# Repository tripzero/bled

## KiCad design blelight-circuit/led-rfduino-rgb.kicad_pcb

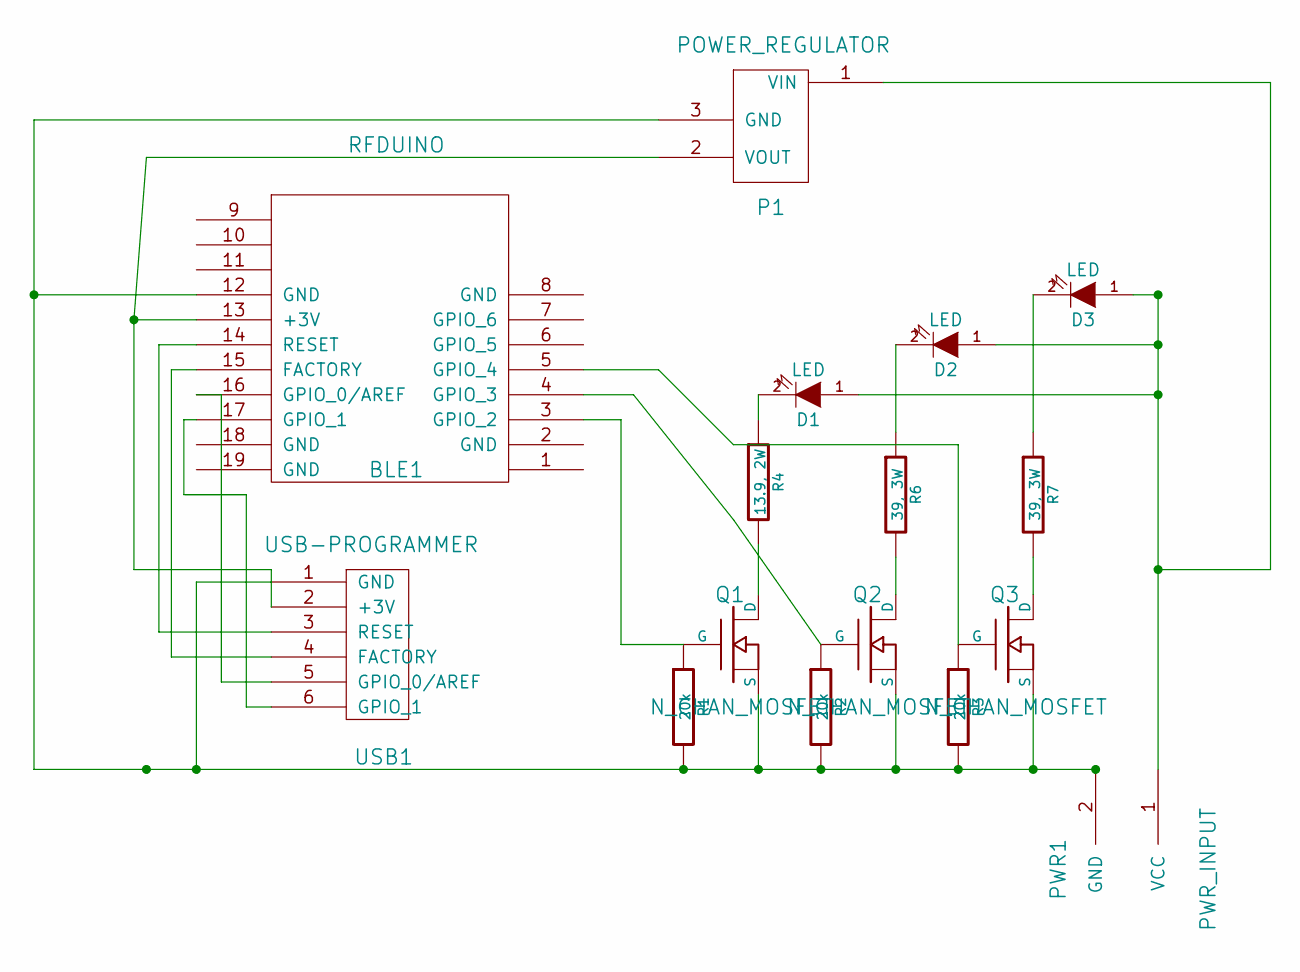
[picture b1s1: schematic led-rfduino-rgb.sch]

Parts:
BLE1: RFDUINO
D1, D2, D3: LED
P1: POWER_REGULATOR
PWR1: PWR_INPUT
Q1, Q2, Q3: N_CHAN_MOSFET
R1, R2, R3: 20k
R4: 13.9, 2W
R6, R7: 39, 3W
USB1: USB-PROGRAMMER

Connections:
unnamed: BLE1.14 (RESET), USB1.3 (RESET)
unnamed: Q3.3 (D), R7.2
unnamed: BLE1.5 (GPIO_4), Q3.2 (G), R3.1
unnamed: Q2.3 (D), R6.2
unnamed: Q1.3 (D), R4.2
unnamed: BLE1.3 (GPIO_2), Q1.2 (G), R1.1
unnamed: BLE1.4 (GPIO_3), Q2.2 (G), R2.1
unnamed: D1.2 (K), R4.1
unnamed: D2.2 (K), R6.1
unnamed: D3.2 (K), R7.1
unnamed: BLE1.17 (GPIO_1), USB1.6 (GPIO_1)
unnamed: BLE1.16 (GPIO_0/AREF), USB1.5 (GPIO_0/AREF)
unnamed: BLE1.15 (FACTORY), USB1.4 (FACTORY)
unnamed: BLE1.13 (+3V), P1.2 (VOUT), USB1.2 (+3V)
unnamed: BLE1.12 (GND), P1.3 (GND), PWR1.2 (GND), Q1.1 (S), Q2.1 (S), Q3.1 (S), R1.2, R2.2, R3.2, USB1.1 (GND)
unnamed: D1.1 (A), D2.1 (A), D3.1 (A), P1.1 (VIN), PWR1.1 (VCC)

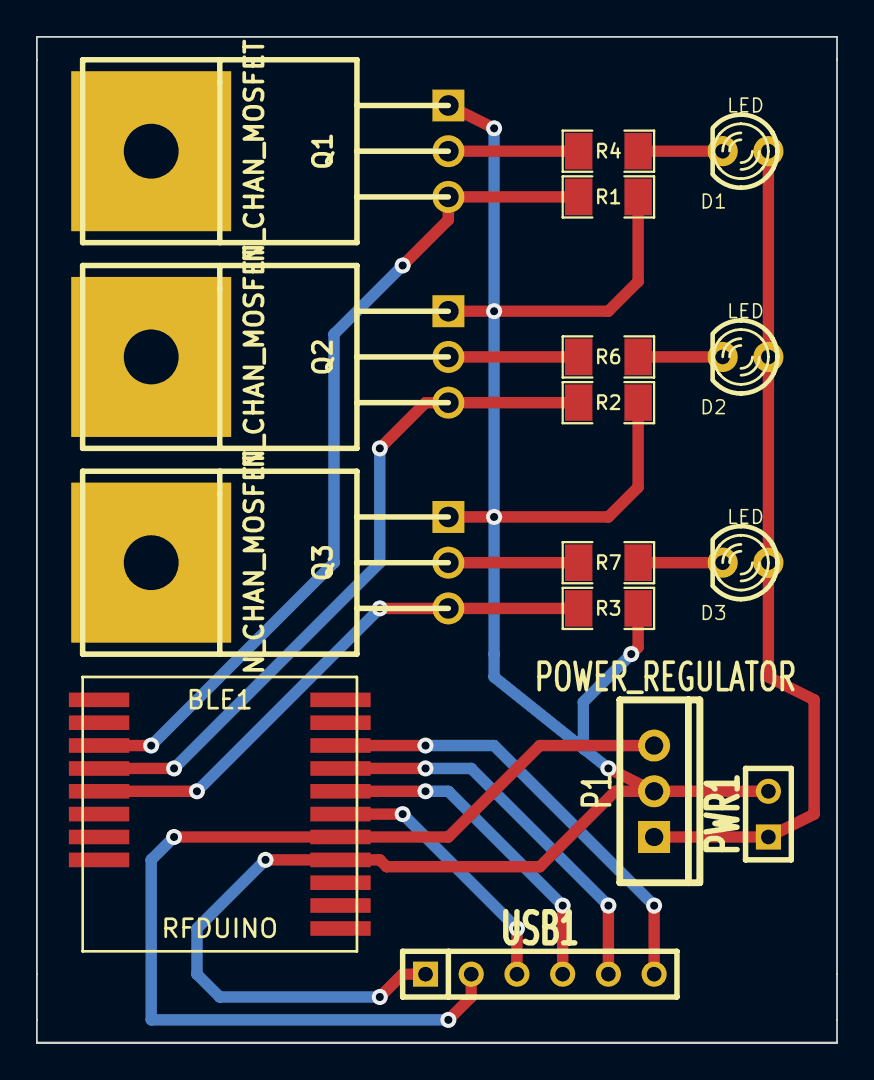
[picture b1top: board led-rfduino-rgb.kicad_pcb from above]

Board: 2 copper layers, 44.5 x 55.9 mm, 16 parts (0 on the bottom side), 16 nets.

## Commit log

2015-02-23 initial add
2015-02-24 somewhat working
2015-02-24 fixed pcb
2015-02-26 more awesome
2015-03-02 mods to the circuit
2015-03-17 lights beginnings
2015-03-21 lightserver working
2015-03-25 updates to the protocol
2015-03-27 removed corners
